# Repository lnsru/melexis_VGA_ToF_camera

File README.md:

# melexis_VGA_ToF_camera
PCB design with the new MLX75027 VGA time of flight sensor

For test pattern acquisition it can be used with Raspberry Pi, for real operation it needs external power supply.

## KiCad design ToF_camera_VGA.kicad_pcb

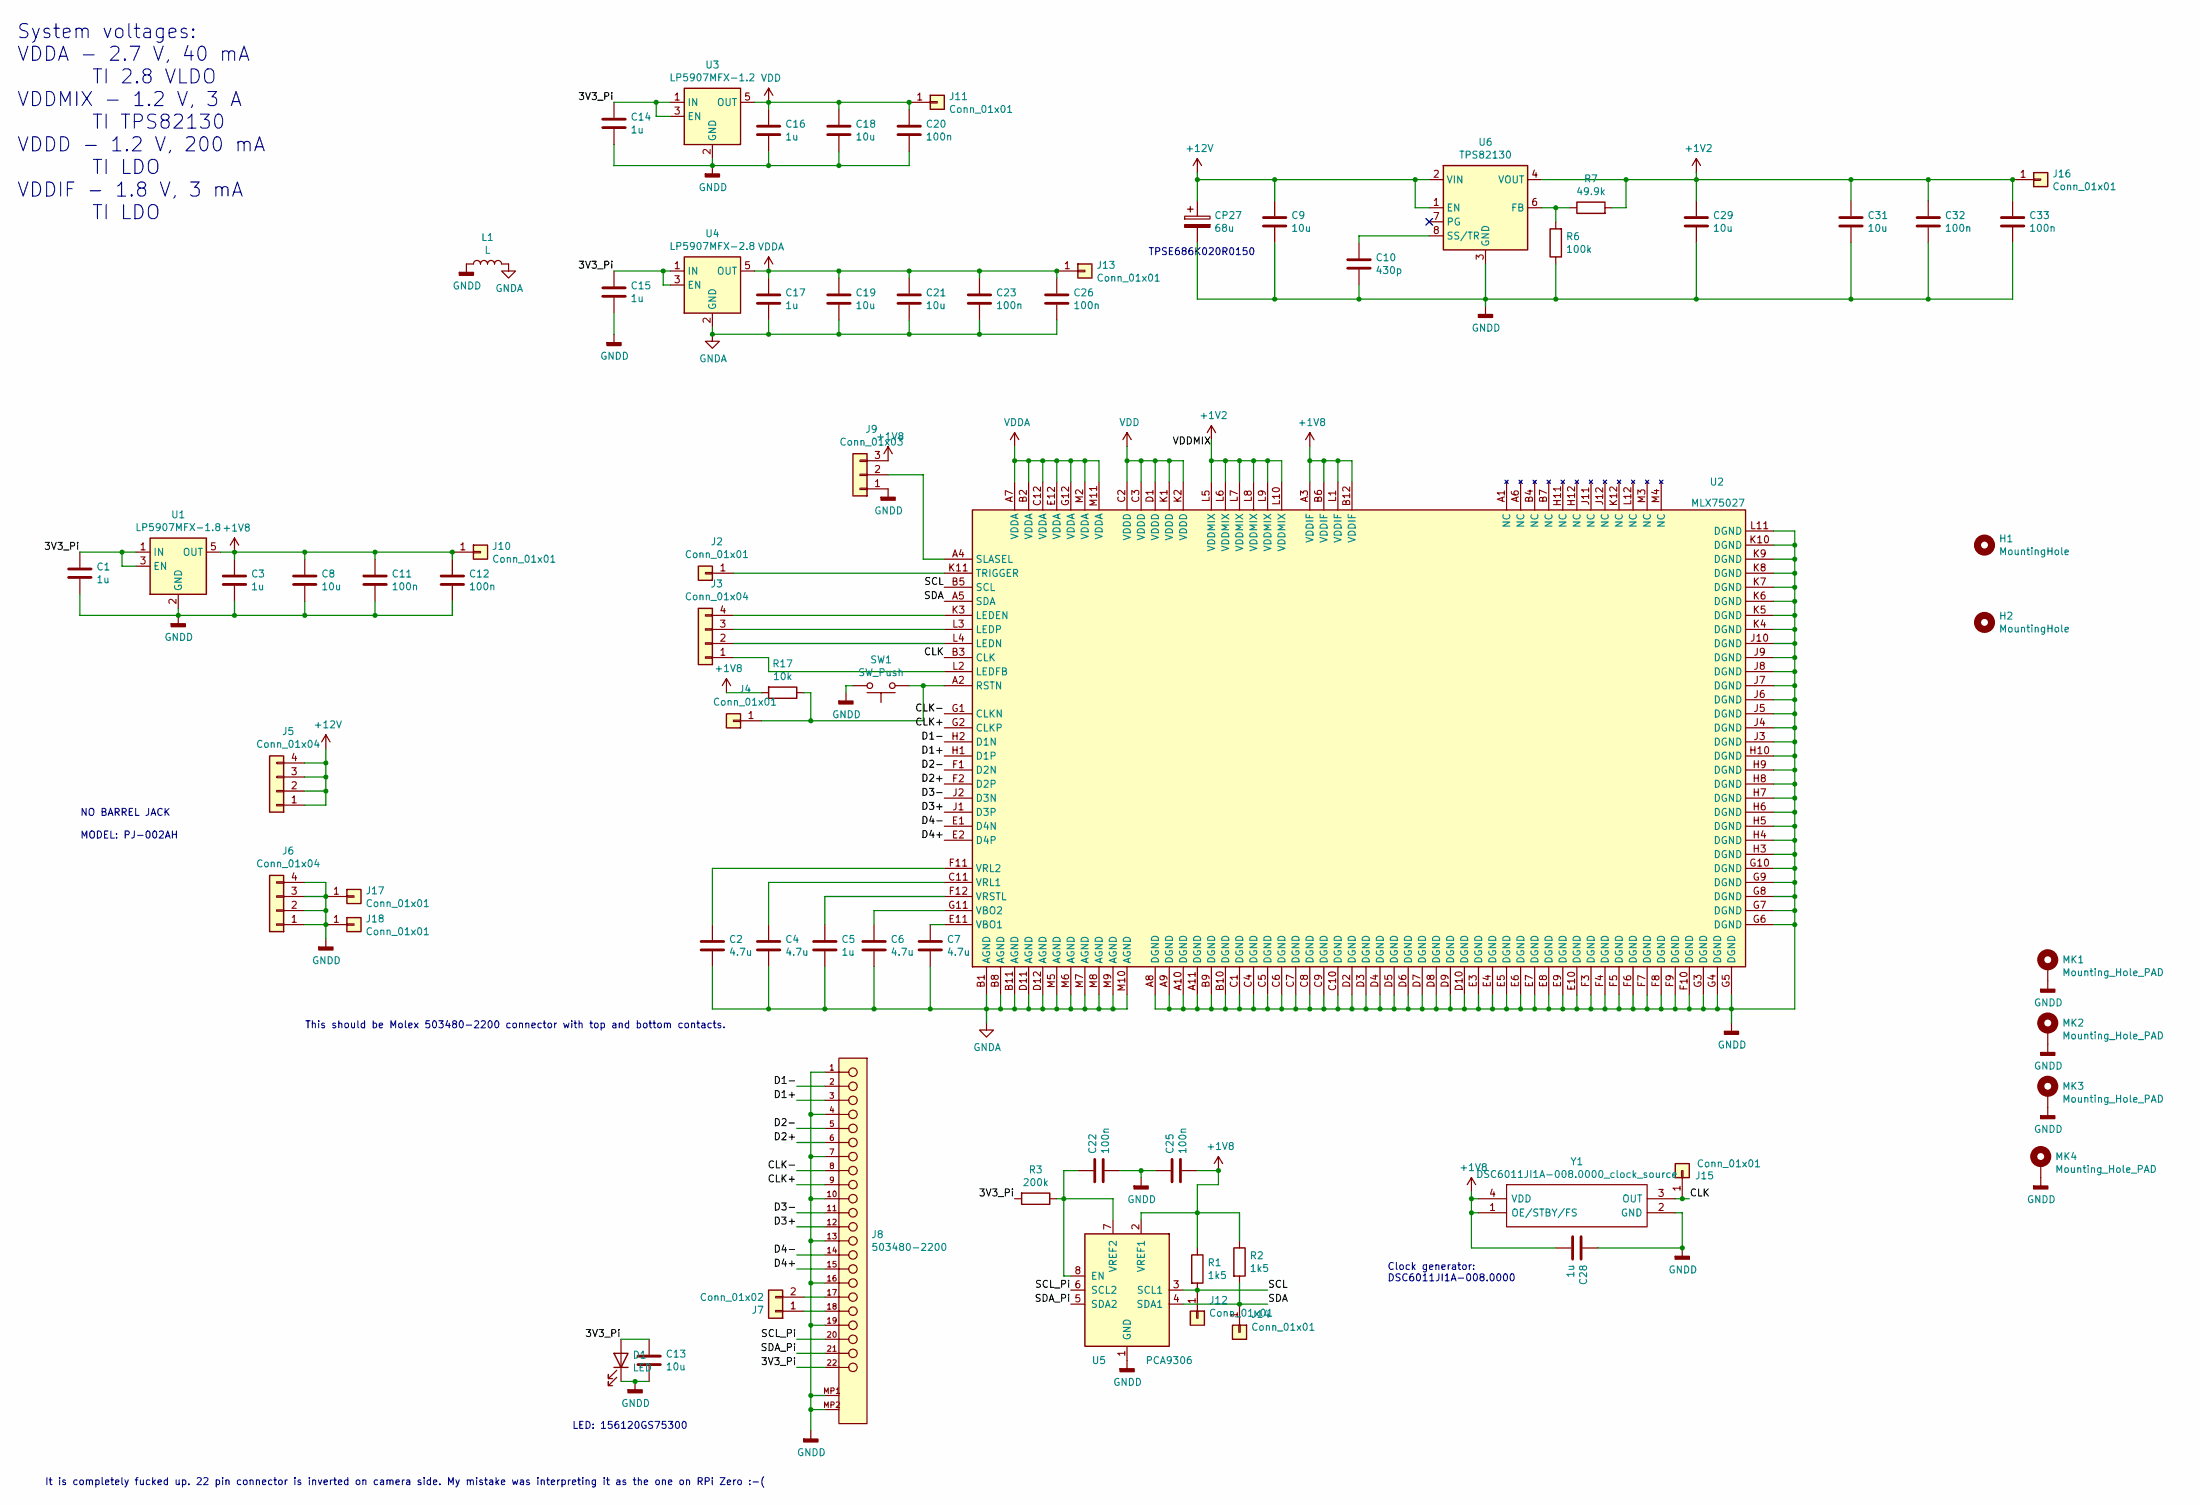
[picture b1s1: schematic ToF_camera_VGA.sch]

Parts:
C1, C3, C5, C14, C15, C16, C17, C28: 1u; C_0805_2012Metric
C2, C4, C6, C7: 4.7u; C_0805_2012Metric
C8, C9, C13, C18, C19, C21, C29, C31: 10u; C_0805_2012Metric
C10: 430p; C_0805_2012Metric
C11, C12, C20, C22, C23, C25, C26, C32, C33: 100n; C_0805_2012Metric
CP27: 68u; CP_EIA-7343-30_AVX-N
D1: LED; LED_1206_3216Metric
H1, H2: MountingHole; MountingHole_1.5mm
J2: Conn_01x01; PinHeader_1x01_P2.54mm_Vertical
J3: Conn_01x04; PinHeader_1x04_P2.54mm_Vertical
J4: Conn_01x01; TestPoint_Pad_D1.5mm
J5, J6: Conn_01x04; PinHeader_2x02_P2.54mm_Vertical
J7: Conn_01x02; R_0603_1608Metric
J8: 503480-2200; Molex-503480-2200; Voltage Max 50V AC (RMS)/DC
J9: Conn_01x03; SolderJumper-3_P1.3mm_Bridged2Bar12_RoundedPad1.0x1.5mm
J10, J12, J14, J16: Conn_01x01; TestPoint_Pad_2.0x2.0mm
J11, J13, J15: Conn_01x01; TestPoint_Pad_1.0x1.0mm
J17, J18: Conn_01x01; TestPoint_Pad_4.0x4.0mm
L1: L; L_1210_3225Metric
MK1, MK2, MK3, MK4: Mounting_Hole_PAD; MountingHole_3.2mm_M3
R1, R2: 1k5; R_0805_2012Metric
R3: 200k; R_0805_2012Metric
R6: 100k; R_0805_2012Metric
R7: 49.9k; R_0805_2012Metric
R17: 10k; R_0805_2012Metric
SW1: SW_Push; SW_SPST_EVPBF
U1: LP5907MFX-1.8; SOT-23-5
U2: MLX75027; MLX75027_NSMD
U3: LP5907MFX-1.2; SOT-23-5
U4: LP5907MFX-2.8; SOT-23-5
U5: PCA9306; SSOP-8_2.95x2.8mm_P0.65mm
U6: TPS82130; Texas_SIL0008D_MicroSiP-8-1EP_2.8x3mm_P0.65mm_EP1.1x1.9mm_T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
Y1: DSC6011JI1A-008.0000_clock_source; DSC6011JI1A0080000_clock_source; Mouser Part Number 579-011JI1A0080000

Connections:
+1V2: C29.1, C31.1, C32.1, C33.1, J16.1, R7.2, U2.L5 (VDDMIX), U2.L6 (VDDMIX), U2.L7 (VDDMIX), U2.L8 (VDDMIX), U2.L9 (VDDMIX), U2.L10 (VDDMIX), U6.4 (VOUT), U6.5 (VOUT)
+1V8: C3.1, C8.1, C11.1, C12.1, C25.2, C28.2, J9.3, J10.1, R1.1, R2.1, R17.2, U1.5 (OUT), U2.A3 (VDDIF), U2.B6 (VDDIF), U2.B12 (VDDIF), U2.L1 (VDDIF), U5.2 (VREF1), Y1.1 (OE/STBY/FS), Y1.4 (VDD)
+12V: C9.1, CP27.1, J5.1, J5.2, J5.3, J5.4, U6.1 (EN), U6.2 (VIN)
/3V3_Pi: C1.1, C13.1, C14.1, C15.1, D1.2 (A), J8.22, R3.2, U1.1 (IN), U1.3 (EN), U3.1 (IN), U3.3 (EN), U4.1 (IN), U4.3 (EN)
/CLK: J15.1, U2.B3 (CLK), Y1.3 (OUT)
/CLK+: J8.9, U2.G2 (CLKP)
/CLK-: J8.8, U2.G1 (CLKN)
/D1+: J8.3, U2.H1 (D1P)
/D1-: J8.2, U2.H2 (D1N)
/D2+: J8.6, U2.F2 (D2P)
/D2-: J8.5, U2.F1 (D2N)
/D3+: J8.12, U2.J1 (D3P)
/D3-: J8.11, U2.J2 (D3N)
/D4+: J8.15, U2.E2 (D4P)
/D4-: J8.14, U2.E1 (D4N)
/SCL: J12.1, R1.2, U2.B5 (SCL), U5.3 (SCL1)
/SCL_Pi: J8.20, U5.6 (SCL2)
/SDA: J14.1, R2.2, U2.A5 (SDA), U5.4 (SDA1)
/SDA_Pi: J8.21, U5.5 (SDA2)
GNDA: C2.2, C4.2, C5.2, C6.2, C7.2, C17.2, C19.2, C21.2, C23.2, C26.2, L1.2, U2.B1 (AGND), U2.B8 (AGND), U2.B11 (AGND), U2.D11 (AGND), U2.D12 (AGND), U2.M5 (AGND), U2.M6 (AGND), U2.M7 (AGND), U2.M8 (AGND), U2.M9 (AGND), U2.M10 (AGND), U4.2 (GND)
GNDD: C1.2, C3.2, C8.2, C9.2, C10.2, C11.2, C12.2, C13.2, C14.2, C15.2, C16.2, C18.2, C20.2, C22.2, C25.1, C28.1, C29.2, C31.2, C32.2, C33.2, CP27.2, D1.1 (K), J6.1, J6.2, J6.3, J6.4, J8.1, J8.4, J8.7, J8.10, J8.13, J8.16, J8.19, J8.MP1, J8.MP2, J9.1, J17.1, J18.1, L1.1, MK1.1, MK2.1, MK3.1, MK4.1, R6.1, SW1.2, U1.2 (GND), U2.A8 (DGND), U2.A9 (DGND), U2.A10 (DGND), U2.A11 (DGND), U2.B9 (DGND), U2.B10 (DGND), U2.C1 (DGND), U2.C4 (DGND), U2.C5 (DGND), U2.C6 (DGND), U2.C7 (DGND), U2.C8 (DGND), U2.C9 (DGND), U2.C10 (DGND), U2.D2 (DGND), U2.D3 (DGND), U2.D4 (DGND), U2.D5 (DGND), U2.D6 (DGND), U2.D7 (DGND), U2.D8 (DGND), U2.D9 (DGND), U2.D10 (DGND), U2.E3 (DGND), U2.E4 (DGND), U2.E5 (DGND), U2.E6 (DGND), U2.E7 (DGND), U2.E8 (DGND), U2.E9 (DGND), U2.E10 (DGND), U2.F3 (DGND), U2.F4 (DGND), U2.F5 (DGND), U2.F6 (DGND), U2.F7 (DGND), U2.F8 (DGND), U2.F9 (DGND), U2.F10 (DGND), U2.G3 (DGND), U2.G4 (DGND), U2.G5 (DGND), U2.G6 (DGND), U2.G7 (DGND), U2.G8 (DGND), U2.G9 (DGND), U2.G10 (DGND), U2.H3 (DGND), U2.H4 (DGND), U2.H5 (DGND), U2.H6 (DGND), U2.H7 (DGND), U2.H8 (DGND), U2.H9 (DGND), U2.H10 (DGND), U2.J3 (DGND), U2.J4 (DGND), U2.J5 (DGND), U2.J6 (DGND), U2.J7 (DGND), U2.J8 (DGND), U2.J9 (DGND), U2.J10 (DGND), U2.K4 (DGND), U2.K5 (DGND), U2.K6 (DGND), U2.K7 (DGND), U2.K8 (DGND), U2.K9 (DGND), U2.K10 (DGND), U2.L11 (DGND), U3.2 (GND), U5.1 (GND), U6.3 (GND), U6.9 (GND), Y1.2 (GND)
unnamed: C2.1, U2.F11 (VRL2)
unnamed: C4.1, U2.C11 (VRL1)
unnamed: C5.1, U2.F12 (VRSTL)
unnamed: C6.1, U2.G11 (VBO2)
unnamed: C7.1, U2.E11 (VBO1)
unnamed: C10.1, U6.8 (SS/TR)
unnamed: C22.1, R3.1, U5.7 (VREF2), U5.8 (EN)
unnamed: J2.1, U2.K11 (TRIGGER)
unnamed: J3.1, U2.L2 (LEDFB)
unnamed: J3.2, U2.L4 (LEDN)
unnamed: J3.3, U2.L3 (LEDP)
unnamed: J3.4, U2.K3 (LEDEN)
unnamed: J4.1, R17.1, SW1.1, U2.A2 (RSTN)
unnamed: J7.1, J8.18
unnamed: J7.2, J8.17
unnamed: J9.2, U2.A4 (SLASEL)
unnamed: R6.2, R7.1, U6.6 (FB)
VDD: C16.1, C18.1, C20.1, J11.1, U2.C2 (VDDD), U2.C3 (VDDD), U2.D1 (VDDD), U2.K1 (VDDD), U2.K2 (VDDD), U3.5 (OUT)
VDDA: C17.1, C19.1, C21.1, C23.1, C26.1, J13.1, U2.A7 (VDDA), U2.B2 (VDDA), U2.C12 (VDDA), U2.E12 (VDDA), U2.G12 (VDDA), U2.M2 (VDDA), U2.M11 (VDDA), U4.5 (OUT)

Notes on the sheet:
System voltages: VDDA - 2.7 V, 40 mA TI 2.8 VLDO VDDMIX - 1.2 V, 3 A TI TPS82130 VDDD - 1.2 V, 200 mA TI LDO VDDIF - 1.8 V, 3 mA TI LDO
LED: 156120GS75300
Clock generator: DSC6011JI1A-008.0000
TPSE686K020R0150
It is completely fucked up. 22 pin connector is inverted on camera side. My mistake was interpreting it as the one on RPi Zero :-(
NO BARREL JACK MODEL: PJ-002AH
This should be Molex 503480-2200 connector with top and bottom contacts.

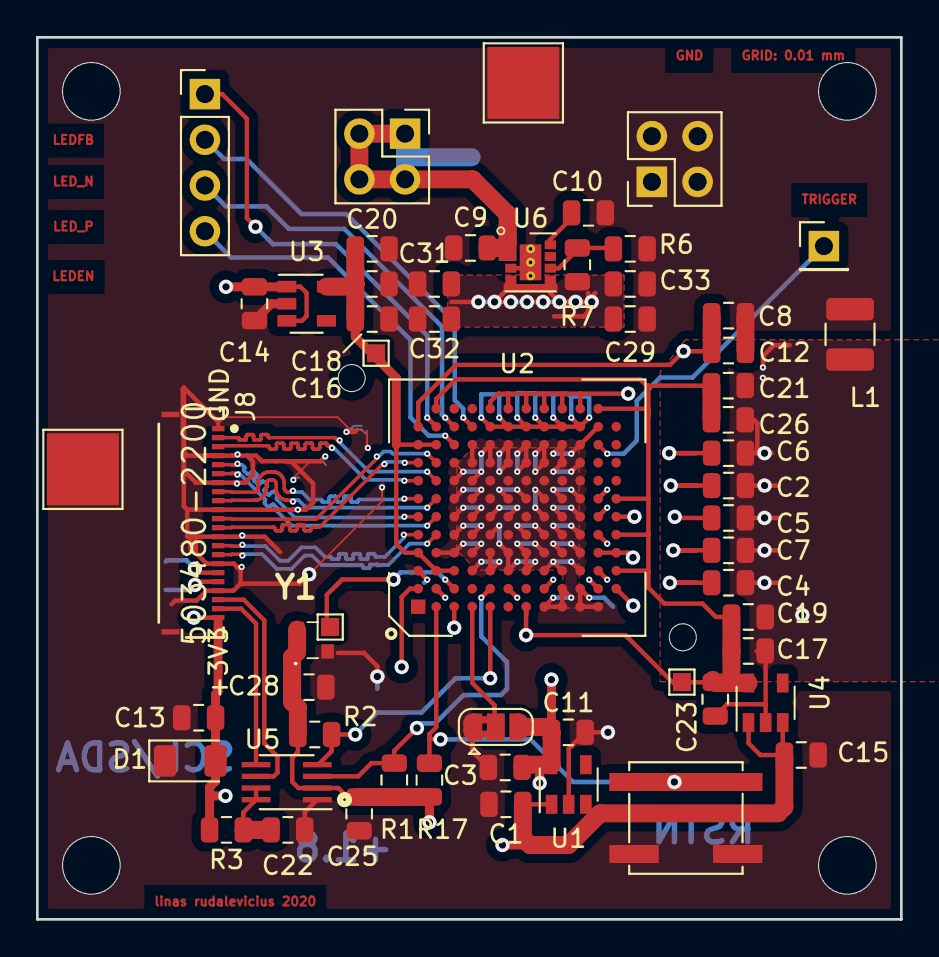
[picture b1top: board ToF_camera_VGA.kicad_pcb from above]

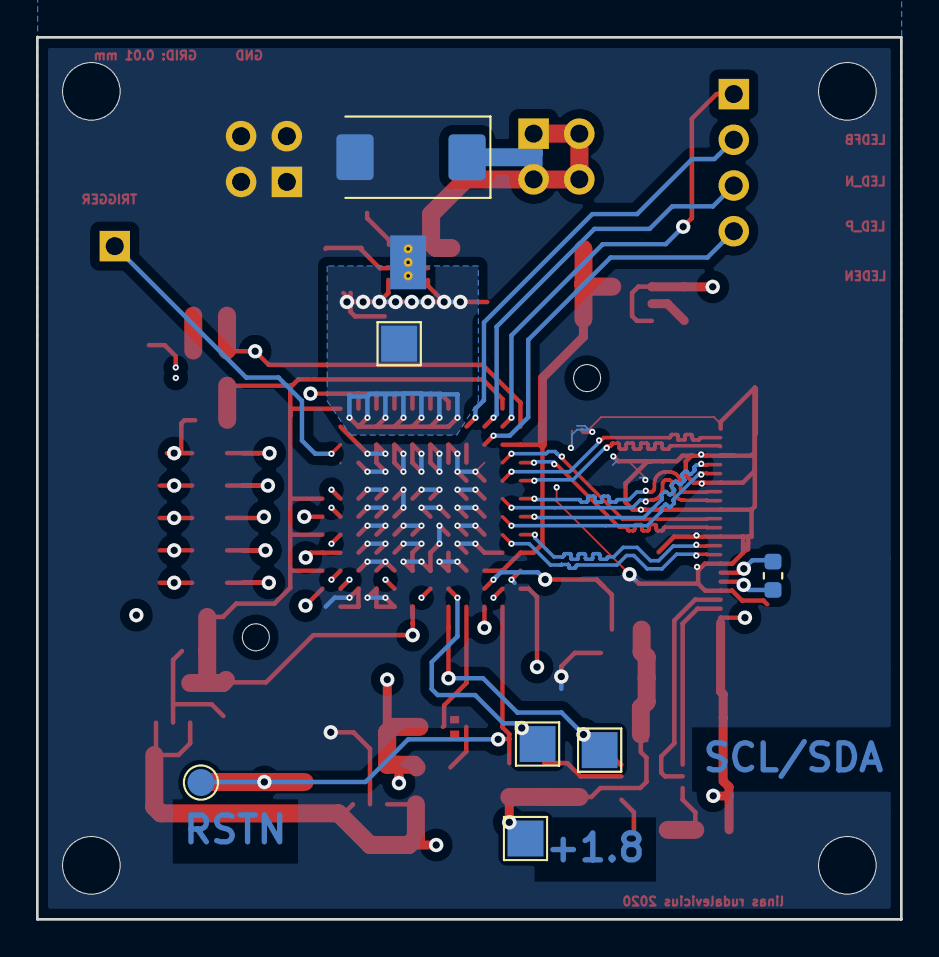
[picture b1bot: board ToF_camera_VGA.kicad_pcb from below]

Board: 4 copper layers, 48.0 x 49.0 mm, 70 parts (7 on the bottom side), 40 nets.

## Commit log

2019-08-06 Inverted connector and re-routed CSI-2 lanes
2019-08-17 Almost there... minor modifications for production needed
2019-08-19 Added filter between analog and digital grounds. Moved to 5.1.4 KiCad version
2019-08-19 Fixed component markings on silkscreen
2019-08-21 Updated BOM
2019-08-25 Minor updates, production read. Added Gerbers
2020-08-08 Version 2 with fixed following issues: 1. clock source added 2. Flat cable connector should be ok 3. I2C level shifter should be ok 4. Power tree simplified, 12 V needed only for VDDMIX, others are g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
2020-08-08 BOM added
2021-11-09 Flat cable connector fixed. The right part is Molex 5034802200
2021-11-09 Picture added
2021-12-08 Delete datasheet directory
    Removed datasheets as asked by vendor.
